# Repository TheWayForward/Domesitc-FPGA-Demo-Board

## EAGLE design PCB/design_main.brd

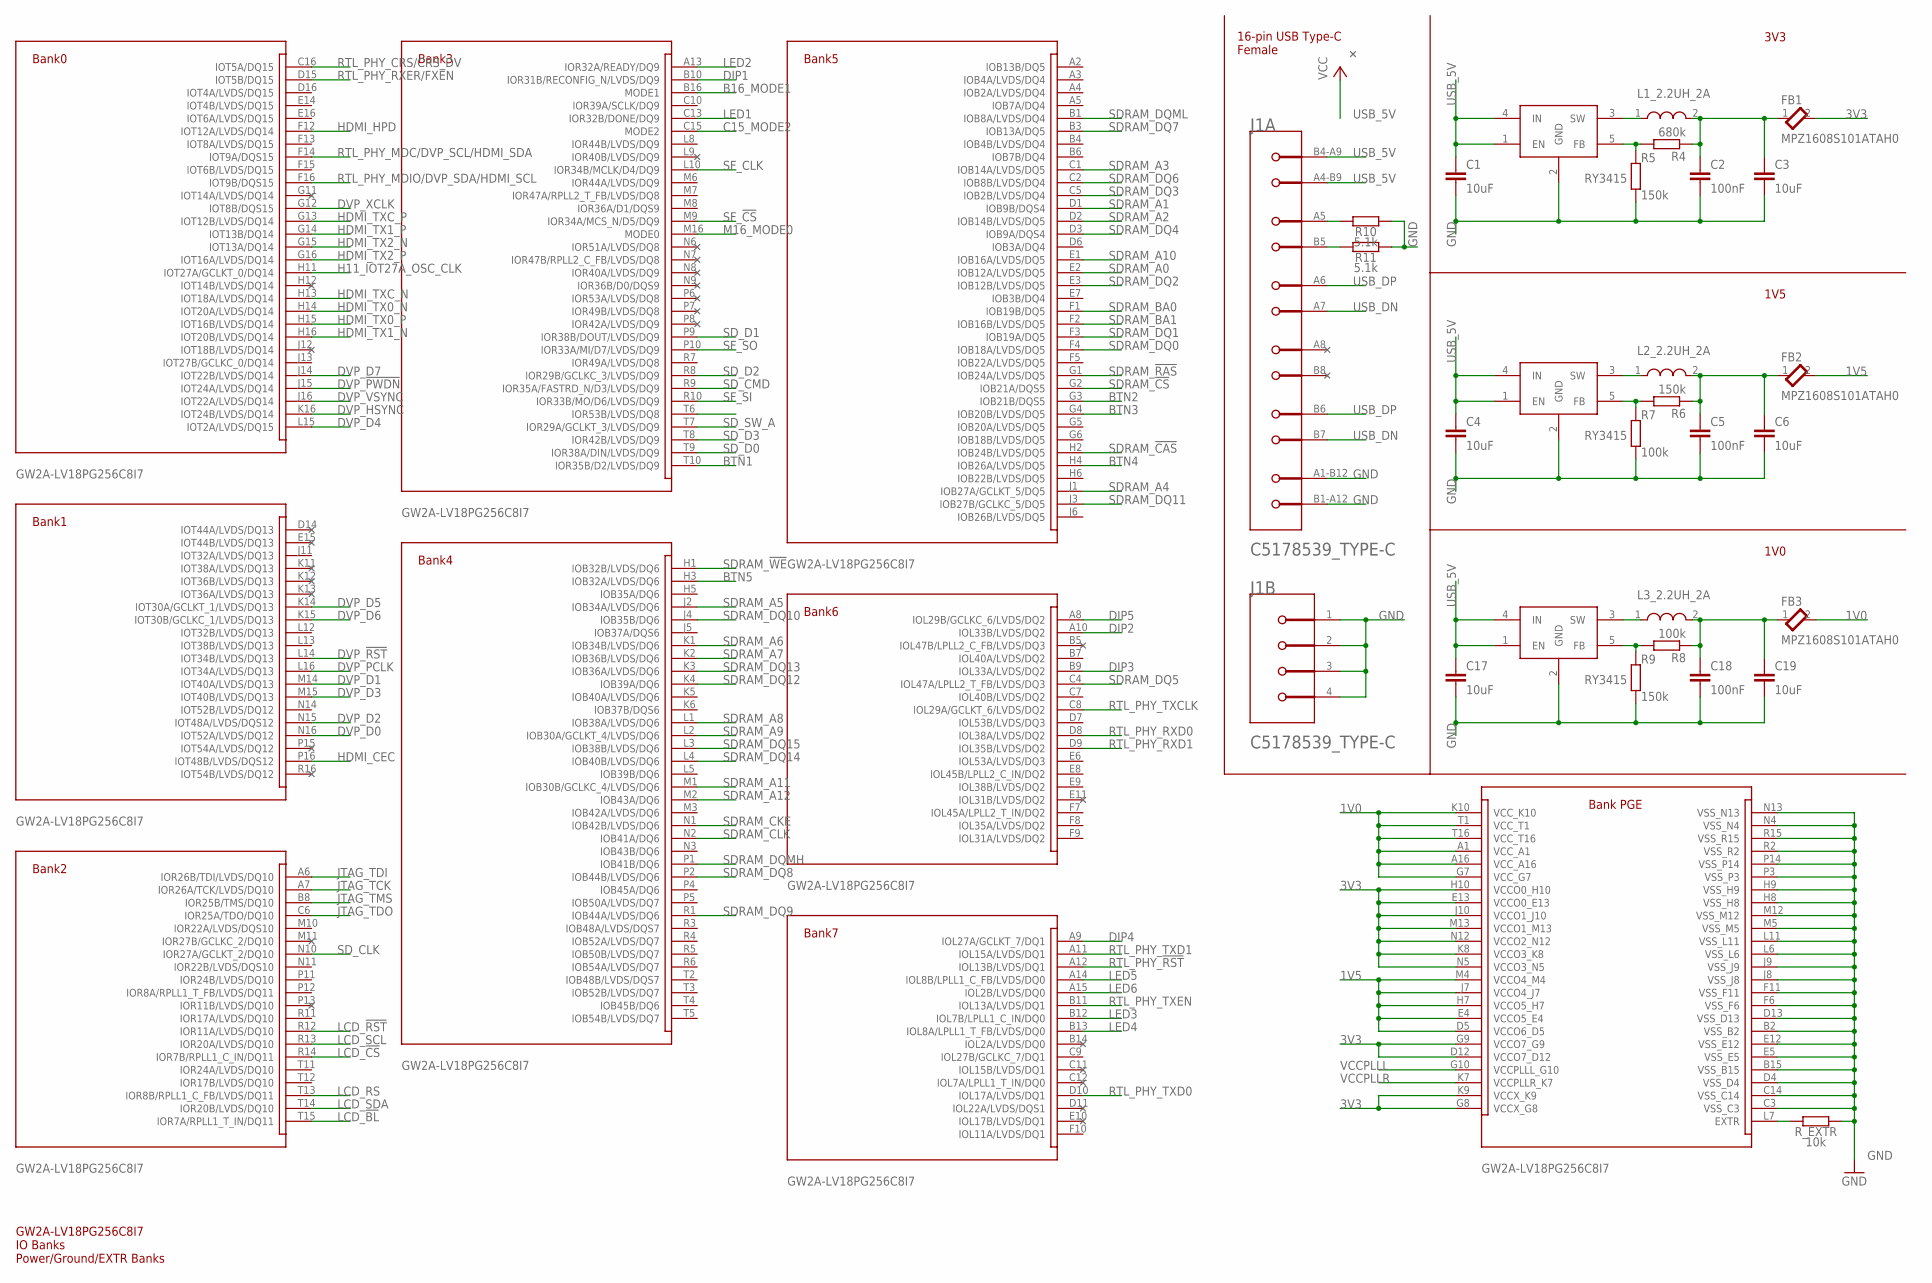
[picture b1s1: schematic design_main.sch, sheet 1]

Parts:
C1, C3, C4, C6, C17, C19: 10uF; C0805
C2, C5, C18: 100nF; C0805
FB1, FB2, FB3: TDK_MPZ1608S101ATAH0TDK_MPZ1608S101ATAH0_0_0; TDK_MPZ1608S101ATAH0_0
J1: C5178539_TYPE-CMOLEX_217179-0001_0_0; C5178539_TYPE-C
L1_2.2UH_2A: L_0805TDK_MLZ2012N6R8LT000_0_0; TDK_MLZ2012N6R8LT000_0
L2_2.2UH_2A, L3_2.2UH_2A: 2.2uH 2A; TDK_MLZ2012N6R8LT000_0
R4: 680k; R0805
R5, R6, R9: 150k; R0805
R7, R8: 100k; R0805
R10, R11: 5.1k; R0805
R_EXTR: 10k; R0805
U$1: GW2A-LV18PG256C8I7; BGA256C100P16X16_1700X1700X155
U$3, U$4, U$5: RY3415

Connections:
1V0: FB3.2, U$1.A1 (VCC_A1), U$1.A16 (VCC_A16), U$1.G7 (VCC_G7), U$1.K10 (VCC_K10), U$1.T1 (VCC_T1), U$1.T16 (VCC_T16); also elsewhere on the board
1V5: FB2.2, U$1.D5 (VCCO6_D5), U$1.E4 (VCCO5_E4), U$1.H7 (VCCO5_H7), U$1.J7 (VCCO4_J7), U$1.M4 (VCCO4_M4); also elsewhere on the board
3V3: FB1.2, U$1.D12 (VCCO7_D12), U$1.E13 (VCCO0_E13), U$1.G8 (VCCX_G8), U$1.G9 (VCCO7_G9), U$1.H10 (VCCO0_H10), U$1.J10 (VCCO1_J10), U$1.K8 (VCCO3_K8), U$1.K9 (VCCX_K9), U$1.M13 (VCCO1_M13), U$1.N5 (VCCO3_N5), U$1.N12 (VCCO2_N12); also elsewhere on the board
B16_MODE1: U$1.B16 (MODE1); also elsewhere on the board
BTN1: U$1.T10 (IOR35B/D2/LVDS/DQ9); also elsewhere on the board
BTN2: U$1.G3 (IOB21B/DQS5); also elsewhere on the board
BTN3: U$1.G4 (IOB20B/LVDS/DQ5); also elsewhere on the board
BTN4: U$1.H4 (IOB26A/LVDS/DQ5); also elsewhere on the board
BTN5: U$1.H3 (IOB32A/LVDS/DQ6); also elsewhere on the board
C15_MODE2: U$1.C15 (MODE2); also elsewhere on the board
DIP1: U$1.B10 (IOR31B/RECONFIG_N/LVDS/DQ9); also elsewhere on the board
DIP2: U$1.A10 (IOL33B/LVDS/DQ2); also elsewhere on the board
DIP3: U$1.B9 (IOL33A/LVDS/DQ2); also elsewhere on the board
DIP4: U$1.A9 (IOL27A/GCLKT_7/DQ1); also elsewhere on the board
DIP5: U$1.A8 (IOL29B/GCLKC_6/LVDS/DQ2); also elsewhere on the board
DVP_!PWDN!: U$1.J15 (IOT24A/LVDS/DQ14); also elsewhere on the board
DVP_!RST!: U$1.L14 (IOT34B/LVDS/DQ13); also elsewhere on the board
DVP_D0: U$1.N16 (IOT52A/LVDS/DQ12); also elsewhere on the board
DVP_D1: U$1.M14 (IOT40A/LVDS/DQ13); also elsewhere on the board
DVP_D2: U$1.N15 (IOT48A/LVDS/DQS12); also elsewhere on the board
DVP_D3: U$1.M15 (IOT40B/LVDS/DQ13); also elsewhere on the board
DVP_D4: U$1.L15 (IOT2A/LVDS/DQ15); also elsewhere on the board
DVP_D5: U$1.K14 (IOT30A/GCLKT_1/LVDS/DQ13); also elsewhere on the board
DVP_D6: U$1.K15 (IOT30B/GCLKC_1/LVDS/DQ13); also elsewhere on the board
DVP_D7: U$1.J14 (IOT22B/LVDS/DQ14); also elsewhere on the board
DVP_HSYNC: U$1.K16 (IOT24B/LVDS/DQ14); also elsewhere on the board
DVP_PCLK: U$1.L16 (IOT34A/LVDS/DQ13); also elsewhere on the board
DVP_VSYNC: U$1.J16 (IOT22A/LVDS/DQ14); also elsewhere on the board
DVP_XCLK: U$1.G12 (IOT8B/DQS15); also elsewhere on the board
GND: C1.1, C2.1, C3.1, C4.1, C5.1, C6.1, C17.1, C18.1, C19.1, J1.1 (MNT_1), J1.2 (MNT_2), J1.3 (MNT_3), J1.4 (MNT_4), J1.A1-B12 (1_GND), J1.B1-A12 (2_GND), R5.2, R7.2, R9.2, R10.1, R11.1, R_EXTR.2, U$1.B2 (VSS_B2), U$1.B15 (VSS_B15), U$1.C3 (VSS_C3), U$1.C14 (VSS_C14), U$1.D4 (VSS_D4), U$1.D13 (VSS_D13), U$1.E5 (VSS_E5), U$1.E12 (VSS_E12), U$1.F6 (VSS_F6), U$1.F11 (VSS_F11), U$1.H8 (VSS_H8), U$1.H9 (VSS_H9), U$1.J8 (VSS_J8), U$1.J9 (VSS_J9), U$1.L6 (VSS_L6), U$1.L11 (VSS_L11), U$1.M5 (VSS_M5), U$1.M12 (VSS_M12), U$1.N4 (VSS_N4), U$1.N13 (VSS_N13), U$1.P3 (VSS_P3), U$1.P14 (VSS_P14), U$1.R2 (VSS_R2), U$1.R15 (VSS_R15), U$3.2 (GND), U$4.2 (GND), U$5.2 (GND); also elsewhere on the board
H11_IOT27A_OSC_CLK: U$1.H11 (IOT27A/GCLKT_0/DQ14); also elsewhere on the board
HDMI_CEC: U$1.P16 (IOT48B/LVDS/DQS12); also elsewhere on the board
HDMI_HPD: U$1.F12 (IOT12A/LVDS/DQ14); also elsewhere on the board
HDMI_TX0_N: U$1.H14 (IOT20A/LVDS/DQ14); also elsewhere on the board
HDMI_TX0_P: U$1.H15 (IOT16B/LVDS/DQ14); also elsewhere on the board
HDMI_TX1_N: U$1.H16 (IOT20B/LVDS/DQ14); also elsewhere on the board
HDMI_TX1_P: U$1.G14 (IOT13B/DQ14); also elsewhere on the board
HDMI_TX2_N: U$1.G15 (IOT13A/DQ14); also elsewhere on the board
HDMI_TX2_P: U$1.G16 (IOT16A/LVDS/DQ14); also elsewhere on the board
HDMI_TXC_N: U$1.H13 (IOT18A/LVDS/DQ14); also elsewhere on the board
HDMI_TXC_P: U$1.G13 (IOT12B/LVDS/DQ14); also elsewhere on the board
JTAG_TCK: U$1.A7 (IOR26A/TCK/LVDS/DQ10); also elsewhere on the board
JTAG_TDI: U$1.A6 (IOR26B/TDI/LVDS/DQ10); also elsewhere on the board
JTAG_TDO: U$1.C6 (IOR25A/TDO/DQ10); also elsewhere on the board
JTAG_TMS: U$1.B8 (IOR25B/TMS/DQ10); also elsewhere on the board
LCD_!BL!: U$1.T15 (IOR7A/RPLL1_T_IN/DQ11); also elsewhere on the board
LCD_!CS!: U$1.R14 (IOR7B/RPLL1_C_IN/DQ11); also elsewhere on the board
LCD_!RST!: U$1.R12 (IOR11A/LVDS/DQ10); also elsewhere on the board
LCD_RS: U$1.T13 (IOR8B/RPLL1_C_FB/LVDS/DQ11); also elsewhere on the board
LCD_SCL: U$1.R13 (IOR20A/LVDS/DQ10); also elsewhere on the board
LCD_SDA: U$1.T14 (IOR20B/LVDS/DQ10); also elsewhere on the board
LED1: U$1.C13 (IOR32B/DONE/DQ9); also elsewhere on the board
LED2: U$1.A13 (IOR32A/READY/DQ9); also elsewhere on the board
LED3: U$1.B12 (IOL7B/LPLL1_C_IN/DQ0); also elsewhere on the board
LED4: U$1.B13 (IOL8A/LPLL1_T_FB/LVDS/DQ0); also elsewhere on the board
LED5: U$1.A14 (IOL8B/LPLL1_C_FB/LVDS/DQ0); also elsewhere on the board
LED6: U$1.A15 (IOL2B/LVDS/DQ0); also elsewhere on the board
M16_MODE0: U$1.M16 (MODE0); also elsewhere on the board
unnamed: R6.2, R7.1, U$4.5 (FB)
unnamed: R_EXTR.1, U$1.L7 (EXTR)
unnamed: L2_2.2UH_2A.1, U$4.3 (SW)
unnamed: C5.2, C6.2, FB2.1, L2_2.2UH_2A.2, R6.1
unnamed: R4.2, R5.1, U$3.5 (FB)
unnamed: L1_2.2UH_2A.1, U$3.3 (SW)
unnamed: C2.2, C3.2, FB1.1, L1_2.2UH_2A.2, R4.1
unnamed: R8.2, R9.1, U$5.5 (FB)
unnamed: L3_2.2UH_2A.1, U$5.3 (SW)
unnamed: C18.2, C19.2, FB3.1, L3_2.2UH_2A.2, R8.1
unnamed: J1.A5 (CC1), R10.2
unnamed: J1.B5 (CC2), R11.2
RTL_PHY_!RST!: U$1.A12 (IOL13B/LVDS/DQ1); also elsewhere on the board
RTL_PHY_CRS/CRS_DV: U$1.C16 (IOT5A/DQ15); also elsewhere on the board
RTL_PHY_MDC/DVP_SCL/HDMI_SDA: U$1.F14 (IOT9A/DQS15); also elsewhere on the board
RTL_PHY_MDIO/DVP_SDA/HDMI_SCL: U$1.F16 (IOT9B/DQS15); also elsewhere on the board
RTL_PHY_RXD0: U$1.D8 (IOL38A/LVDS/DQ2); also elsewhere on the board
RTL_PHY_RXD1: U$1.D9 (IOL35B/LVDS/DQ2); also elsewhere on the board
RTL_PHY_RXER/FXEN: U$1.D15 (IOT5B/DQ15); also elsewhere on the board
RTL_PHY_TXCLK: U$1.C8 (IOL29A/GCLKT_6/LVDS/DQ2); also elsewhere on the board
RTL_PHY_TXD0: U$1.D10 (IOL17A/LVDS/DQ1); also elsewhere on the board
RTL_PHY_TXD1: U$1.A11 (IOL15A/LVDS/DQ1); also elsewhere on the board
RTL_PHY_TXEN: U$1.B11 (IOL13A/LVDS/DQ1); also elsewhere on the board
SDRAM_!CAS!: U$1.H2 (IOB24B/LVDS/DQ5); also elsewhere on the board
SDRAM_!CS!: U$1.G2 (IOB21A/DQS5); also elsewhere on the board
SDRAM_!RAS!: U$1.G1 (IOB24A/LVDS/DQ5); also elsewhere on the board
SDRAM_!WE!: U$1.H1 (IOB32B/LVDS/DQ6); also elsewhere on the board
SDRAM_A0: U$1.E2 (IOB12A/LVDS/DQ5); also elsewhere on the board
SDRAM_A1: U$1.D1 (IOB9B/DQS4); also elsewhere on the board
SDRAM_A2: U$1.D2 (IOB14B/LVDS/DQ5); also elsewhere on the board
SDRAM_A3: U$1.C1 (IOB14A/LVDS/DQ5); also elsewhere on the board
SDRAM_A4: U$1.J1 (IOB27A/GCLKT_5/DQ5); also elsewhere on the board
SDRAM_A5: U$1.J2 (IOB34A/LVDS/DQ6); also elsewhere on the board
SDRAM_A6: U$1.K1 (IOB34B/LVDS/DQ6); also elsewhere on the board
SDRAM_A7: U$1.K2 (IOB36B/LVDS/DQ6); also elsewhere on the board
SDRAM_A8: U$1.L1 (IOB38A/LVDS/DQ6); also elsewhere on the board
SDRAM_A9: U$1.L2 (IOB30A/GCLKT_4/LVDS/DQ6); also elsewhere on the board
SDRAM_A10: U$1.E1 (IOB16A/LVDS/DQ5); also elsewhere on the board
SDRAM_A11: U$1.M1 (IOB30B/GCLKC_4/LVDS/DQ6); also elsewhere on the board
SDRAM_A12: U$1.M2 (IOB43A/DQ6); also elsewhere on the board
SDRAM_BA0: U$1.F1 (IOB19B/DQ5); also elsewhere on the board
SDRAM_BA1: U$1.F2 (IOB16B/LVDS/DQ5); also elsewhere on the board
SDRAM_CKE: U$1.N1 (IOB42B/LVDS/DQ6); also elsewhere on the board
SDRAM_CLK: U$1.N2 (IOB41A/DQ6); also elsewhere on the board
SDRAM_DQ0: U$1.F4 (IOB18A/LVDS/DQ5); also elsewhere on the board
SDRAM_DQ1: U$1.F3 (IOB19A/DQ5); also elsewhere on the board
SDRAM_DQ2: U$1.E3 (IOB12B/LVDS/DQ5); also elsewhere on the board
SDRAM_DQ3: U$1.C5 (IOB2B/LVDS/DQ4); also elsewhere on the board
SDRAM_DQ4: U$1.D3 (IOB9A/DQS4); also elsewhere on the board
SDRAM_DQ5: U$1.C4 (IOL47A/LPLL2_T_FB/LVDS/DQ3); also elsewhere on the board
SDRAM_DQ6: U$1.C2 (IOB8B/LVDS/DQ4); also elsewhere on the board
SDRAM_DQ7: U$1.B3 (IOB13A/DQ5); also elsewhere on the board
SDRAM_DQ8: U$1.P2 (IOB44B/LVDS/DQ6); also elsewhere on the board
SDRAM_DQ9: U$1.R1 (IOB44A/LVDS/DQ6); also elsewhere on the board
SDRAM_DQ10: U$1.J4 (IOB35B/DQ6); also elsewhere on the board
SDRAM_DQ11: U$1.J3 (IOB27B/GCLKC_5/DQ5); also elsewhere on the board
SDRAM_DQ12: U$1.K4 (IOB39A/DQ6); also elsewhere on the board
SDRAM_DQ13: U$1.K3 (IOB36A/LVDS/DQ6); also elsewhere on the board
SDRAM_DQ14: U$1.L4 (IOB40B/LVDS/DQ6); also elsewhere on the board
SDRAM_DQ15: U$1.L3 (IOB38B/LVDS/DQ6); also elsewhere on the board
SDRAM_DQMH: U$1.P1 (IOB41B/DQ6); also elsewhere on the board
SDRAM_DQML: U$1.B1 (IOB8A/LVDS/DQ4); also elsewhere on the board
SD_CLK: U$1.N10 (IOR27A/GCLKT_2/DQ10); also elsewhere on the board
SD_CMD: U$1.R9 (IOR35A/FASTRD_N/D3/LVDS/DQ9); also elsewhere on the board
SD_D0: U$1.T9 (IOR38A/DIN/LVDS/DQ9); also elsewhere on the board
SD_D1: U$1.P9 (IOR38B/DOUT/LVDS/DQ9); also elsewhere on the board
SD_D2: U$1.R8 (IOR29B/GCLKC_3/LVDS/DQ9); also elsewhere on the board
SD_D3: U$1.T8 (IOR42B/LVDS/DQ9); also elsewhere on the board
SD_SW_A: U$1.T7 (IOR29A/GCLKT_3/LVDS/DQ9); also elsewhere on the board
SF_!CS!: U$1.M9 (IOR34A/MCS_N/D5/DQ9); also elsewhere on the board
SF_CLK: U$1.L10 (IOR34B/MCLK/D4/DQ9); also elsewhere on the board
SF_SI: U$1.R10 (IOR33B/MO/D6/LVDS/DQ9); also elsewhere on the board
SF_SO: U$1.P10 (IOR33A/MI/D7/LVDS/DQ9); also elsewhere on the board
USB_5V: C1.2, C4.2, C17.2, J1.A4-B9 (1_VBUS), J1.B4-A9 (2_VBUS), U$3.1 (EN), U$3.4 (IN), U$4.1 (EN), U$4.4 (IN), U$5.1 (EN), U$5.4 (IN); also elsewhere on the board
USB_DN: J1.A7 (DN1), J1.B7 (DN2); also elsewhere on the board
USB_DP: J1.A6 (DP1), J1.B6 (DP2); also elsewhere on the board
VCCPLLL: U$1.G10 (VCCPLLL_G10); also elsewhere on the board
VCCPLLR: U$1.K7 (VCCPLLR_K7); also elsewhere on the board

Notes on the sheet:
3V3
1V5
1V0
16-pin USB Type-C Female
GW2A-LV18PG256C8I7 IO Banks Power/Ground/EXTR Banks

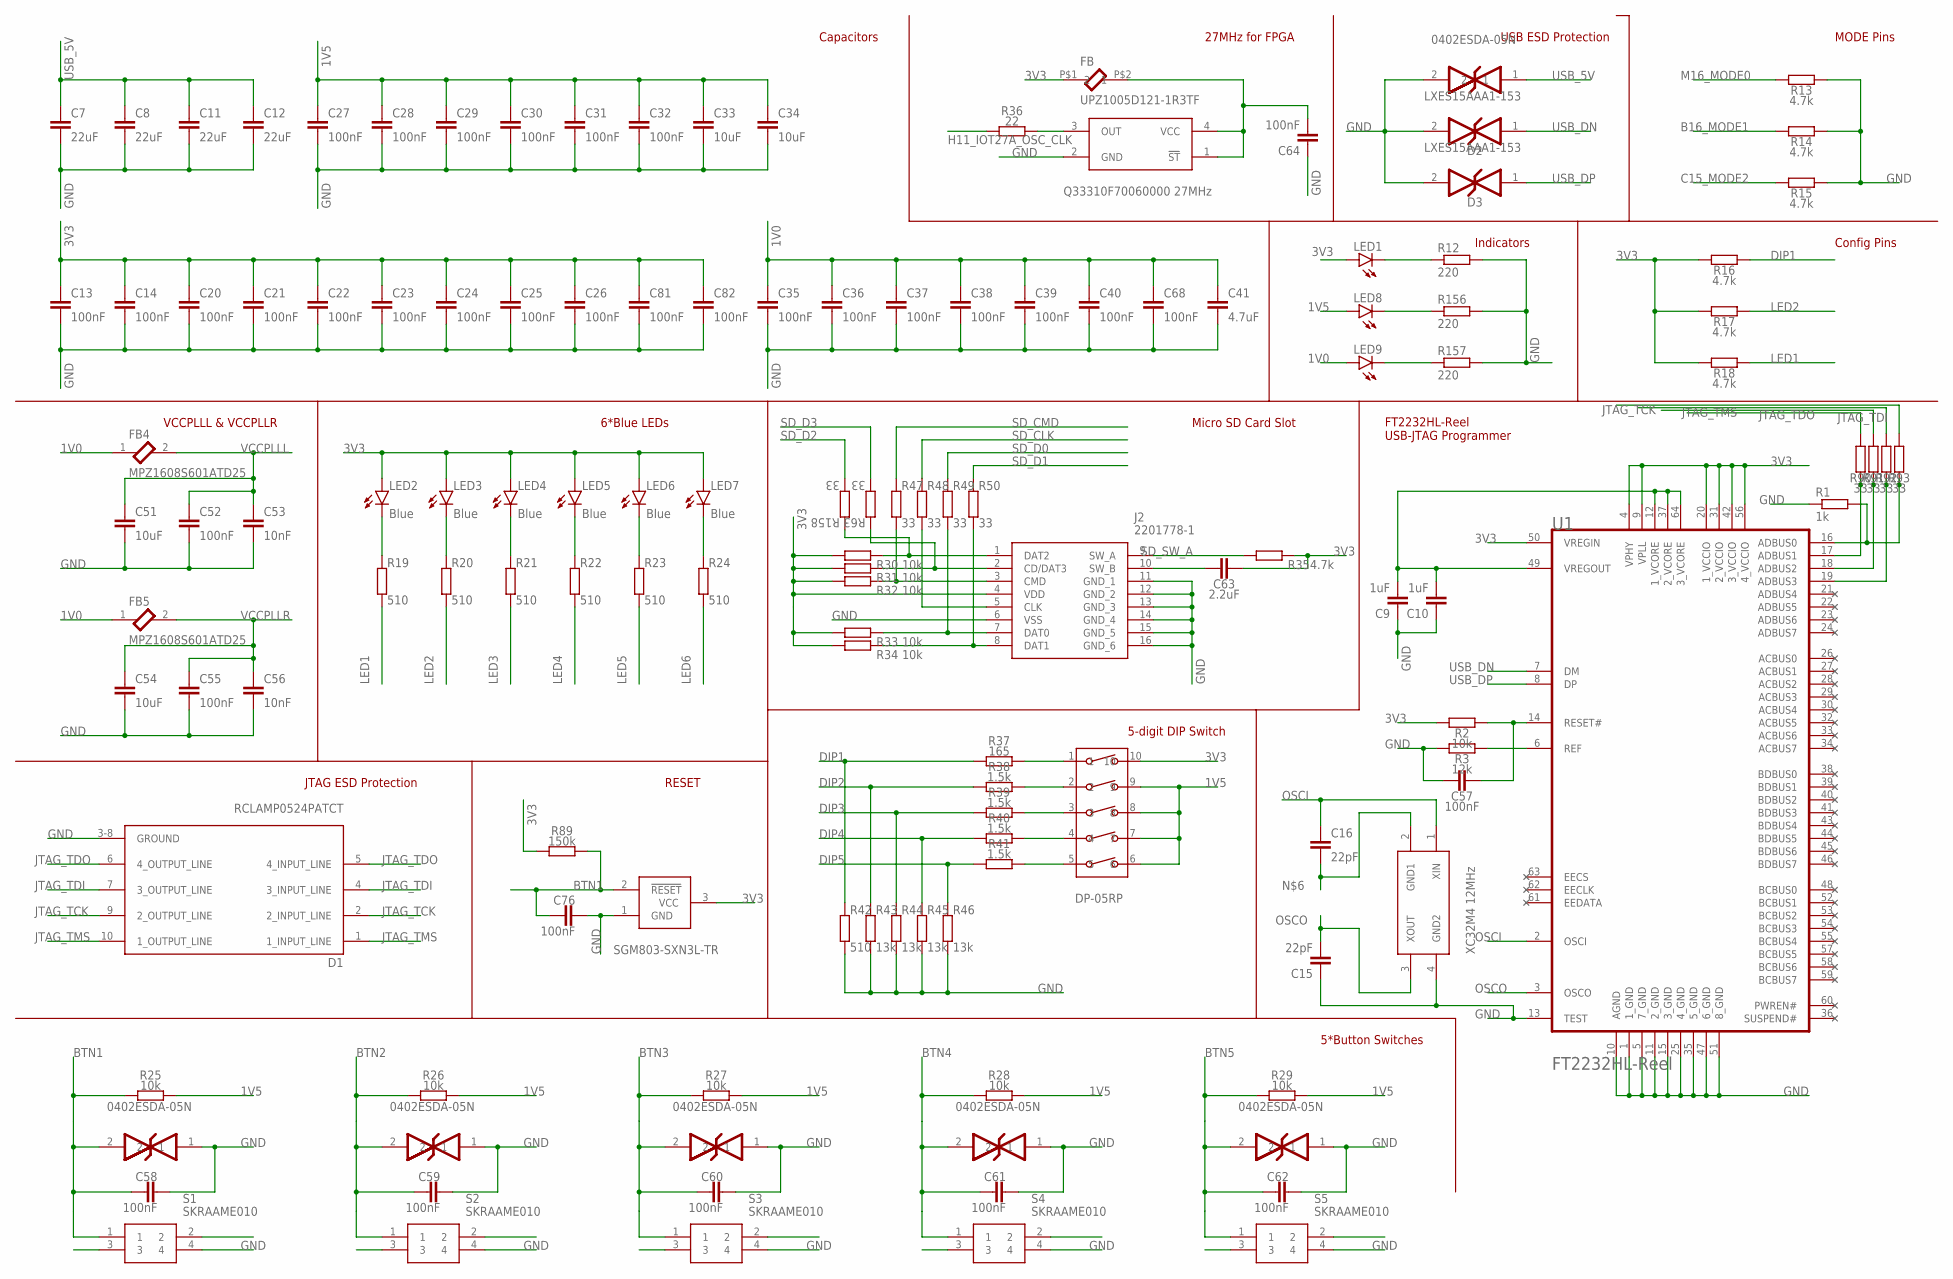
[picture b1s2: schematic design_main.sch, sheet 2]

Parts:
C7, C8, C11, C12: 22uF; C0805
C9, C10: 1uF; C0805
C13, C14, C20, C21, C22, C23, C24, C25, C26, C27, C28, C29, C30, C31, C32, C35, C36, C37, C38, C39, C40, C52, C55, C57, C58, C59, C60, C61, C62, C64, C68, C76, C81, C82: 100nF; C0805
C15, C16: 22pF; C0805
C33, C34, C51, C54: 10uF; C0805
C41: 4.7uF; C0805
C53, C56: 10nF; C0805
C63: 2.2uF; C0805
D1: SEMTECH_RCLAMP0524PATCTSEMTECH_RCLAMP0524PATCT_0_0; SEMTECH_RCLAMP0524PATCT_0
D2, D3: MURATA_LXES15AAA1-153MURATA_LXES15AAA1-153_0_0; MURATA_LXES15AAA1-153_0
FB: UPZ1005D121-1R3TF
FB4, FB5: TDK_MPZ1608S601ATD25TDK_MPZ1608S601ATD25_0_0; TDK_MPZ1608S601ATD25_0
J2: 2201778-1; 22017781
LED1, LED8, LED9: LEDSML0805; SML0805
LED2, LED3, LED4, LED5, LED6, LED7: Blue; SML0805
R1: 1k; R0805
R2, R25, R26, R27, R28, R29, R30, R31, R32, R33, R34: 10k; R0805
R3: 12k; R0805
R12, R156, R157: 220; R0805
R13, R14, R15, R16, R17, R18, R35: 4.7k; R0805
R19, R20, R21, R22, R23, R24, R42: 510; R0805
R36: 22; R0805
R37: 165; R0805
R38, R39, R40, R41: 1.5k; R0805
R43, R44, R45, R46: 13k; R0805
R47, R48, R49, R50, R63, R90, R91, R92, R93, R158: 33; R0805
R89: 150k; R0805
S1, S2, S3, S4, S5: SKRAAME010
U1: FTDI_FT2232HL-REELFTDI_FT2232HL-REEL_0_0; FTDI_FT2232HL-REEL_0
U$2: XC32M4-12MHZ
U$6, U$7, U$8, U$9, U$10, U$11: 0402ESDA-05N
U$13: DP-05RP
U$15: Q33310F70060000-27MHZ
U$16: SGM803-SXN3L-TR

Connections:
1V0: C35.2, C36.2, C37.2, C38.2, C39.2, C40.2, C41.2, C68.2, FB4.1, FB5.1, LED9.A; also elsewhere on the board
1V5: C27.2, C28.2, C29.2, C30.2, C31.2, C32.2, C33.2, C34.2, LED8.A, R25.2, R26.2, R27.2, R28.2, R29.2, U$13.6, U$13.7, U$13.8, U$13.9; also elsewhere on the board
3V3: C13.2, C14.2, C20.2, C21.2, C22.2, C23.2, C24.2, C25.2, C26.2, C63.1, C81.2, C82.2, FB.P$1 (1), J2.4 (VDD), LED1.A, LED2.A, LED3.A, LED4.A, LED5.A, LED6.A, LED7.A, R2.1, R16.2, R17.2, R18.2, R30.1, R31.1, R32.1, R33.1, R34.1, R35.2, R89.1, U1.4 (VPHY), U1.9 (VPLL), U1.20 (1_VCCIO), U1.31 (2_VCCIO), U1.42 (3_VCCIO), U1.50 (VREGIN), U1.56 (4_VCCIO), U$13.10, U$16.3 (VCC); also elsewhere on the board
B16_MODE1: R14.2; also elsewhere on the board
BTN1: C58.2, C76.2, R25.1, R89.2, S1.1, U$7.2, U$16.2 (!RESET!); also elsewhere on the board
BTN2: C59.2, R26.1, S2.1, U$8.2; also elsewhere on the board
BTN3: C60.2, R27.1, S3.1, U$9.2; also elsewhere on the board
BTN4: C61.2, R28.1, S4.1, U$10.2; also elsewhere on the board
BTN5: C62.2, R29.1, S5.1, U$11.2; also elsewhere on the board
C15_MODE2: R15.2; also elsewhere on the board
DIP1: R16.1, R37.1, R42.2; also elsewhere on the board
DIP2: R38.1, R43.2; also elsewhere on the board
DIP3: R39.1, R44.2; also elsewhere on the board
DIP4: R40.1, R45.2; also elsewhere on the board
DIP5: R41.1, R46.2; also elsewhere on the board
GND: C7.1, C8.1, C9.1, C10.1, C11.1, C12.1, C13.1, C14.1, C15.1, C20.1, C21.1, C22.1, C23.1, C24.1, C25.1, C26.1, C27.1, C28.1, C29.1, C30.1, C31.1, C32.1, C33.1, C34.1, C35.1, C36.1, C37.1, C38.1, C39.1, C40.1, C41.1, C51.1, C52.1, C53.1, C54.1, C55.1, C56.1, C57.2, C58.1, C59.1, C60.1, C61.1, C62.1, C64.1, C68.1, C76.1, C81.1, C82.1, D1.3-8 (GROUND), D2.2, D3.2, J2.6 (VSS), J2.11 (GND_1), J2.12 (GND_2), J2.13 (GND_3), J2.14 (GND_4), J2.15 (GND_5), J2.16 (GND_6), R1.1, R3.1, R12.2, R13.1, R14.1, R15.1, R42.1, R43.1, R44.1, R45.1, R46.1, R156.2, R157.2, S1.4, S2.4, S3.4, S4.4, S5.4, U1.1 (1_GND), U1.5 (7_GND), U1.10 (AGND), U1.11 (2_GND), U1.13 (TEST), U1.15 (3_GND), U1.25 (4_GND), U1.35 (5_GND), U1.47 (6_GND), U1.51 (8_GND), U$2.4 (GND2), U$6.2, U$7.1, U$8.1, U$9.1, U$10.1, U$11.1, U$15.2 (GND), U$16.1 (GND); also elsewhere on the board
H11_IOT27A_OSC_CLK: R36.2; also elsewhere on the board
JTAG_TCK: D1.2 (2_INPUT_LINE), D1.9 (2_OUTPUT_LINE), R93.1; also elsewhere on the board
JTAG_TDI: D1.4 (3_INPUT_LINE), D1.7 (3_OUTPUT_LINE), R90.1; also elsewhere on the board
JTAG_TDO: D1.5 (4_INPUT_LINE), D1.6 (4_OUTPUT_LINE), R91.1; also elsewhere on the board
JTAG_TMS: D1.1 (1_INPUT_LINE), D1.10 (1_OUTPUT_LINE), R92.1; also elsewhere on the board
LED1: R18.1, R19.2; also elsewhere on the board
LED2: R17.1, R20.2; also elsewhere on the board
LED3: R21.2; also elsewhere on the board
LED4: R22.2; also elsewhere on the board
LED5: R23.2; also elsewhere on the board
LED6: R24.2; also elsewhere on the board
M16_MODE0: R13.2; also elsewhere on the board
unnamed: R39.2, U$13.3
unnamed: C16.1, U$2.2 (GND1)
unnamed: R3.2, U1.6 (REF)
unnamed: C57.1, R2.2, U1.14 (RESET#)
unnamed: C63.2, J2.10 (SW_B)
unnamed: J2.2 (CD/DAT3), R31.2, R63.1
unnamed: C9.2, C10.2, U1.12 (1_VCORE), U1.37 (2_VCORE), U1.49 (VREGOUT), U1.64 (3_VCORE)
unnamed: LED1.C, R12.1
unnamed: J2.3 (CMD), R32.2, R47.2
unnamed: LED2.C, R19.1
unnamed: LED3.C, R20.1
unnamed: LED4.C, R21.1
unnamed: LED5.C, R22.1
unnamed: LED6.C, R23.1
unnamed: LED7.C, R24.1
unnamed: C64.2, FB.P$2 (2), U$15.1 (!ST!), U$15.4 (VCC)
unnamed: R36.1, U$15.3 (OUT)
unnamed: R37.2, U$13.1
unnamed: R38.2, U$13.2
unnamed: R40.2, U$13.4
unnamed: R41.2, U$13.5
unnamed: J2.5 (CLK), R48.2
unnamed: J2.7 (DAT0), R33.2, R49.2
unnamed: J2.8 (DAT1), R34.2, R50.2
unnamed: J2.1 (DAT2), R30.2, R158.1
unnamed: R1.2, R93.2, U1.16 (ADBUS0)
unnamed: R90.2, U1.17 (ADBUS1)
unnamed: R91.2, U1.18 (ADBUS2)
unnamed: R92.2, U1.19 (ADBUS3)
unnamed: LED8.C, R156.1
unnamed: LED9.C, R157.1
OSCI: C16.2, U1.2 (OSCI), U$2.1 (XIN)
OSCO: C15.2, U1.3 (OSCO), U$2.3 (XOUT)
SD_CLK: R48.1; also elsewhere on the board
SD_CMD: R47.1; also elsewhere on the board
SD_D0: R49.1; also elsewhere on the board
SD_D1: R50.1; also elsewhere on the board
SD_D2: R158.2; also elsewhere on the board
SD_D3: R63.2; also elsewhere on the board
SD_SW_A: J2.9 (SW_A), R35.1; also elsewhere on the board
USB_5V: C7.2, C8.2, C11.2, C12.2, U$6.1; also elsewhere on the board
USB_DN: D2.1, U1.7 (DM); also elsewhere on the board
USB_DP: D3.1, U1.8 (DP); also elsewhere on the board
VCCPLLL: C51.2, C52.2, C53.2, FB4.2; also elsewhere on the board
VCCPLLR: C54.2, C55.2, C56.2, FB5.2; also elsewhere on the board

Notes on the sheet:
Capacitors
27MHz for FPGA
USB ESD Protection
MODE Pins
Indicators
Config Pins
FT2232HL-Reel USB-JTAG Programmer
Micro SD Card Slot
6*Blue LEDs
VCCPLLL & VCCPLLR
RESET
JTAG ESD Protection
5-digit DIP Switch
5*Button Switches

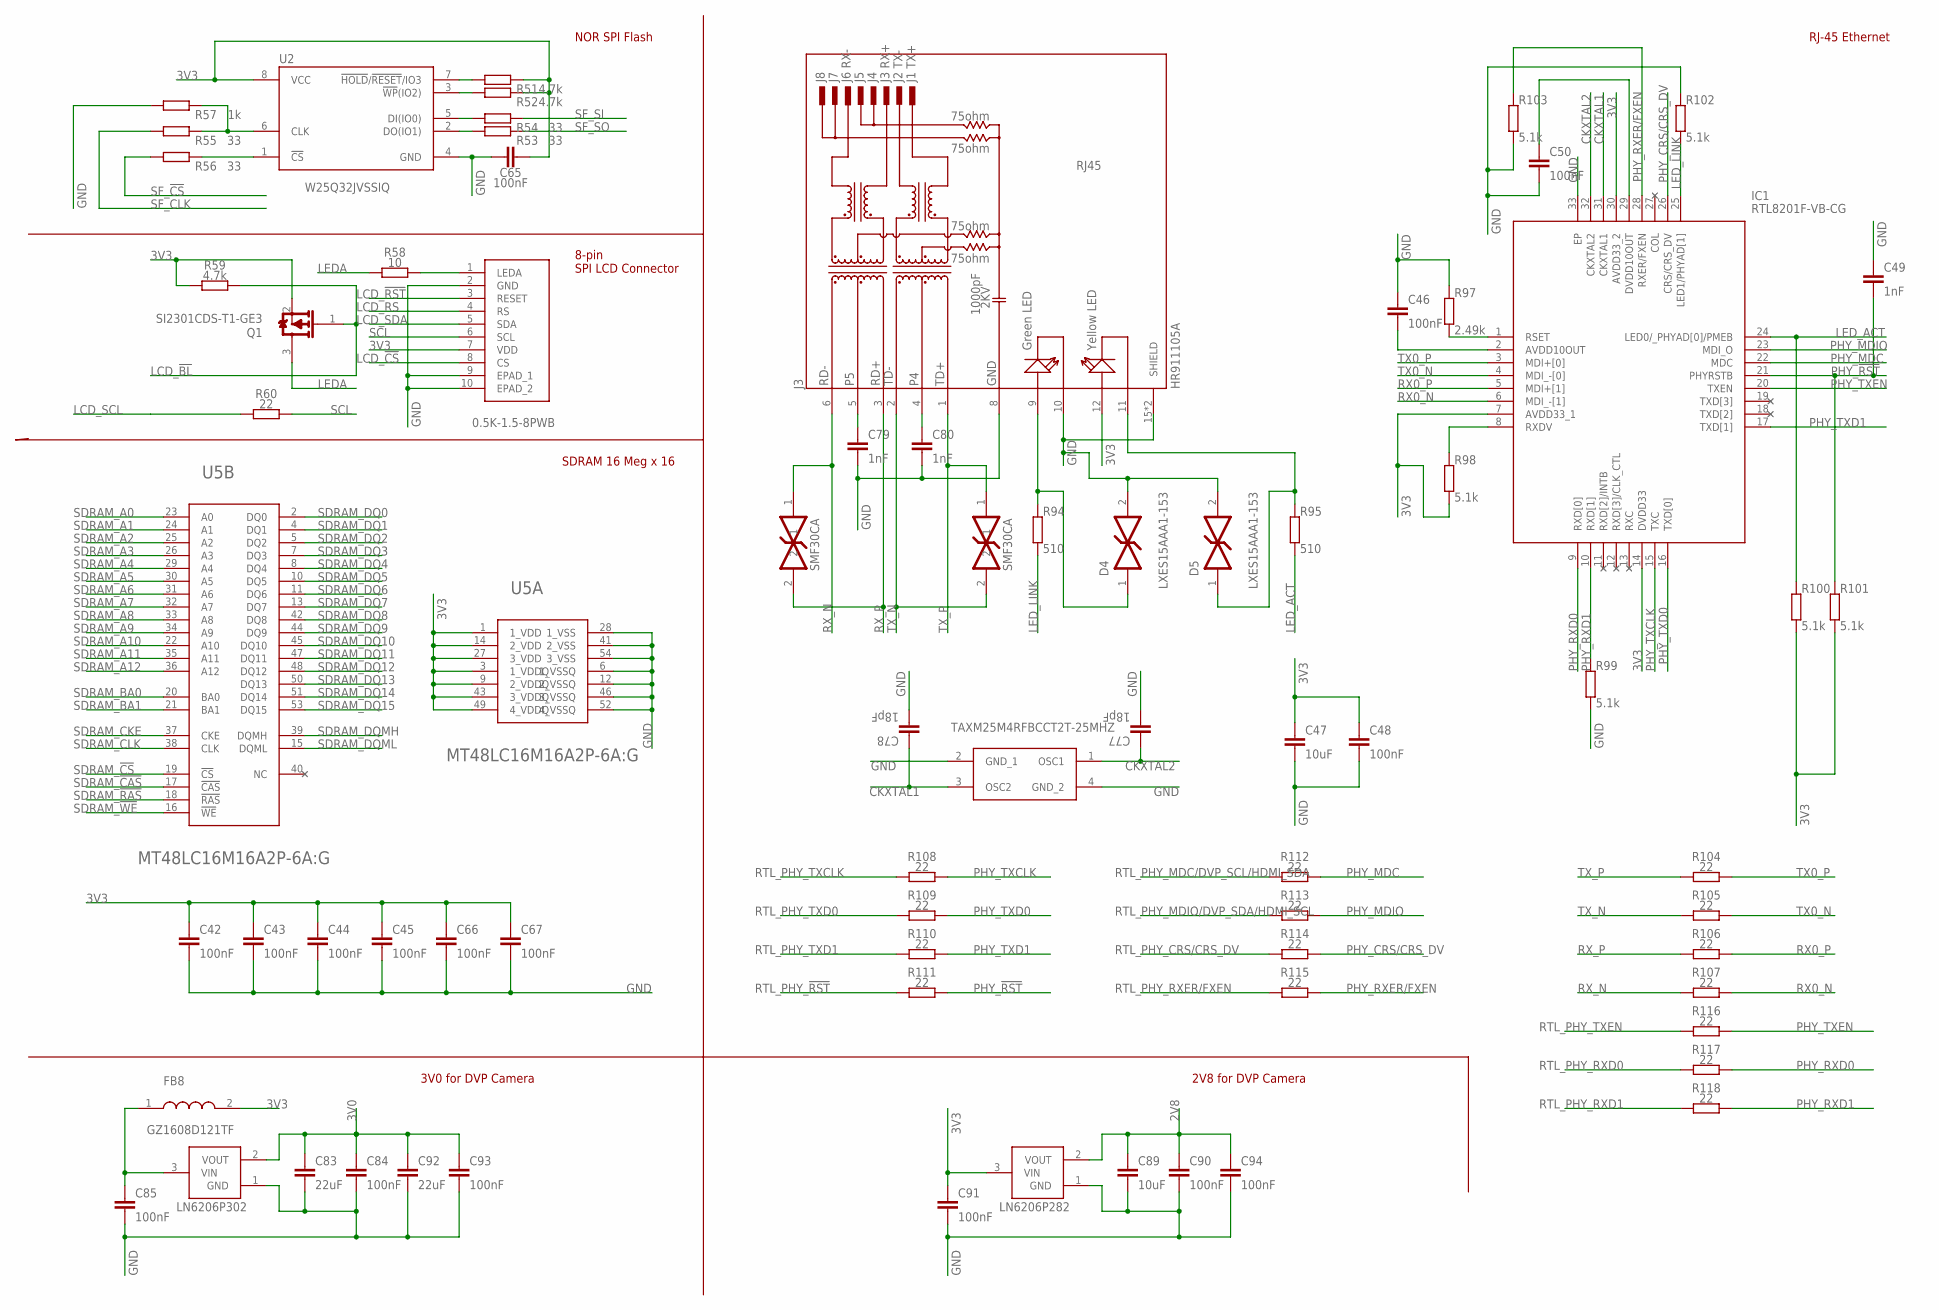
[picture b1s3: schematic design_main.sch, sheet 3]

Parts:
C42, C43, C44, C45, C46, C48, C50, C65, C66, C67, C84, C85, C90, C91, C93, C94: 100nF; C0805
C47, C89: 10uF; C0805
C49, C79, C80: 1nF; C0805
C77, C78: 18pF; C0805
C83, C92: 22uF; C0805
D4, D5: MURATA_LXES15AAA1-153MURATA_LXES15AAA1-153_0_0; MURATA_LXES15AAA1-153_0
FB8: SUNLORD_GZ1608D121TFSUNLORD_GZ1608D121TF_0_0; SUNLORD_GZ1608D121TF_0
IC1: RTL8201F-VB-CG; QFN50P500X500X100-33N
J3: HR911105A; HANRUN_HR911105A
Q1: VISHAY_SI2301CDS-T1-GE3VISHAY_SI2301CDS-T1-GE3_0_0; VISHAY_SI2301CDS-T1-GE3_0
R51, R52, R59: 4.7k; R0805
R53, R54, R55, R56: 33; R0805
R57: 1k; R0805
R58: 10; R0805
R60, R104, R105, R106, R107, R108, R109, R110, R111, R112, R113, R114, R115, R116, R117, R118: 22; R0805
R94, R95: 510; R0805
R97: 2.49k; R0805
R98, R99, R100, R101, R102, R103: 5.1k; R0805
U2: WINBOND_W25Q32JVSSIQWINBOND_W25Q32JVSSIQ_0_0; WINBOND_W25Q32JVSSIQ_0
U5: MICRON_MT48LC16M16A2P-6A-GMICRON_MT48LC16M16A2P-6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; MICRON_MT48LC16M16A2P-6A-G_0
U$14: 0.5K-1.5-8PWB
U$17: TAXM25M4RFBCCT2T-25MHZ
U$18, U$19: SMF30CA
U$20: LN6206P302
U$22: LN6206P282

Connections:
2V8: C89.2, C90.2, C94.2, U$22.2 (VOUT); also elsewhere on the board
3V0: C83.2, C84.2, C92.2, C93.2, U$20.2 (VOUT); also elsewhere on the board
3V3: C42.2, C43.2, C44.2, C45.2, C47.2, C48.2, C65.1, C66.2, C67.2, C91.2, FB8.2, IC1.7 (AVDD33_1), IC1.14 (DVDD33), IC1.30 (AVDD33_2), J3.12 (YA), Q1.2 (S), R51.2, R52.2, R59.1, R98.1, R100.1, R101.1, U2.8 (VCC), U5.1 (1_VDD), U5.3 (1_VDDQ), U5.9 (2_VDDQ), U5.14 (2_VDD), U5.27 (3_VDD), U5.43 (3_VDDQ), U5.49 (4_VDDQ), U$14.7 (VDD), U$22.3 (VIN); also elsewhere on the board
CKXTAL1: C78.2, IC1.31 (CKXTAL1), U$17.3 (OSC2)
CKXTAL2: C77.2, IC1.32 (CKXTAL2), U$17.1 (OSC1)
GND: C42.1, C43.1, C44.1, C45.1, C46.2, C47.1, C48.1, C49.2, C50.1, C65.2, C66.1, C67.1, C77.1, C78.1, C79.1, C80.1, C83.1, C84.1, C85.1, C89.1, C90.1, C91.1, C92.1, C93.1, C94.1, D4.2, D5.2, IC1.33 (EP), J3.8 (GND), J3.10 (GC), J3.15 (SHIELD), J3.16 (SHIELD), R57.1, R97.1, R99.1, R102.1, R103.2, U2.4 (GND), U5.6 (1_VSSQ), U5.12 (2_VSSQ), U5.28 (1_VSS), U5.41 (2_VSS), U5.46 (3_VSSQ), U5.52 (4_VSSQ), U5.54 (3_VSS), U$14.2 (GND), U$14.9 (EPAD_1), U$14.10 (EPAD_2), U$17.2 (GND_1), U$17.4 (GND_2), U$20.1 (GND), U$22.1 (GND); also elsewhere on the board
LCD_!BL!: Q1.1 (G), R59.2; also elsewhere on the board
LCD_!CS!: U$14.8 (CS); also elsewhere on the board
LCD_!RST!: U$14.3 (RESET); also elsewhere on the board
LCD_RS: U$14.4 (RS); also elsewhere on the board
LCD_SCL: R60.1; also elsewhere on the board
LCD_SDA: U$14.5 (SDA); also elsewhere on the board
LEDA: Q1.3 (D), R58.1
LED_ACT: IC1.24 (LED0/_PHYAD[0]/PMEB), R95.2, R100.2
LED_LINK: IC1.25 (LED1/PHYAD[1]), R94.2, R102.2
unnamed: R52.1, U2.3 (!WP!(IO2))
unnamed: R58.2, U$14.1 (LEDA)
unnamed: R51.1, U2.7 (!HOLD!/!RESET!/IO3)
unnamed: R53.1, U2.2 (DO(IO1))
unnamed: R54.1, U2.5 (DI(IO0))
unnamed: R55.2, R57.2, U2.6 (CLK)
unnamed: R56.2, U2.1 (!CS!)
unnamed: IC1.1 (RSET), R97.2
unnamed: C46.1, IC1.2 (AVDD10OUT)
unnamed: C79.2, J3.5
unnamed: C80.2, J3.4
unnamed: D4.1, J3.9 (GA), R94.1
unnamed: D5.1, J3.11 (YC), R95.1
unnamed: IC1.8 (RXDV), R98.2
unnamed: C50.2, IC1.29 (DVDD10OUT)
unnamed: C85.2, FB8.1, U$20.3 (VIN)
PHY_!RST!: C49.1, IC1.21 (PHYRSTB), R101.2, R111.2
PHY_CRS/CRS_DV: IC1.26 (CRS/CRS_DV), R114.2
PHY_MDC: IC1.22 (MDC), R112.2
PHY_MDIO: IC1.23 (MDI_O), R113.2
PHY_RXD0: IC1.9 (RXD[0]), R117.2
PHY_RXD1: IC1.10 (RXD[1]), R99.2, R118.2
PHY_RXER/FXEN: IC1.28 (RXER/FXEN), R103.1, R115.2
PHY_TXCLK: IC1.15 (TXC), R108.2
PHY_TXD0: IC1.16 (TXD[0]), R109.2
PHY_TXD1: IC1.17 (TXD[1]), R110.2
PHY_TXEN: IC1.20 (TXEN), R116.2
RTL_PHY_!RST!: R111.1; also elsewhere on the board
RTL_PHY_CRS/CRS_DV: R114.1; also elsewhere on the board
RTL_PHY_MDC/DVP_SCL/HDMI_SDA: R112.1; also elsewhere on the board
RTL_PHY_MDIO/DVP_SDA/HDMI_SCL: R113.1; also elsewhere on the board
RTL_PHY_RXD0: R117.1; also elsewhere on the board
RTL_PHY_RXD1: R118.1; also elsewhere on the board
RTL_PHY_RXER/FXEN: R115.1; also elsewhere on the board
RTL_PHY_TXCLK: R108.1; also elsewhere on the board
RTL_PHY_TXD0: R109.1; also elsewhere on the board
RTL_PHY_TXD1: R110.1; also elsewhere on the board
RTL_PHY_TXEN: R116.1; also elsewhere on the board
RX0_N: IC1.6 (MDI_-[1]), R107.2
RX0_P: IC1.5 (MDI+[1]), R106.2
RX_N: J3.6 (RD-), R107.1, U$18.1
RX_P: J3.3 (RD+), R106.1, U$18.2
SCL: R60.2, U$14.6 (SCL)
SDRAM_!CAS!: U5.17 (!CAS!); also elsewhere on the board
SDRAM_!CS!: U5.19 (!CS!); also elsewhere on the board
SDRAM_!RAS!: U5.18 (!RAS!); also elsewhere on the board
SDRAM_!WE!: U5.16 (!WE!); also elsewhere on the board
SDRAM_A0: U5.23 (A0); also elsewhere on the board
SDRAM_A1: U5.24 (A1); also elsewhere on the board
SDRAM_A2: U5.25 (A2); also elsewhere on the board
SDRAM_A3: U5.26 (A3); also elsewhere on the board
SDRAM_A4: U5.29 (A4); also elsewhere on the board
SDRAM_A5: U5.30 (A5); also elsewhere on the board
SDRAM_A6: U5.31 (A6); also elsewhere on the board
SDRAM_A7: U5.32 (A7); also elsewhere on the board
SDRAM_A8: U5.33 (A8); also elsewhere on the board
SDRAM_A9: U5.34 (A9); also elsewhere on the board
SDRAM_A10: U5.22 (A10); also elsewhere on the board
SDRAM_A11: U5.35 (A11); also elsewhere on the board
SDRAM_A12: U5.36 (A12); also elsewhere on the board
SDRAM_BA0: U5.20 (BA0); also elsewhere on the board
SDRAM_BA1: U5.21 (BA1); also elsewhere on the board
SDRAM_CKE: U5.37 (CKE); also elsewhere on the board
SDRAM_CLK: U5.38 (CLK); also elsewhere on the board
SDRAM_DQ0: U5.2 (DQ0); also elsewhere on the board
SDRAM_DQ1: U5.4 (DQ1); also elsewhere on the board
SDRAM_DQ2: U5.5 (DQ2); also elsewhere on the board
SDRAM_DQ3: U5.7 (DQ3); also elsewhere on the board
SDRAM_DQ4: U5.8 (DQ4); also elsewhere on the board
SDRAM_DQ5: U5.10 (DQ5); also elsewhere on the board
SDRAM_DQ6: U5.11 (DQ6); also elsewhere on the board
SDRAM_DQ7: U5.13 (DQ7); also elsewhere on the board
SDRAM_DQ8: U5.42 (DQ8); also elsewhere on the board
SDRAM_DQ9: U5.44 (DQ9); also elsewhere on the board
SDRAM_DQ10: U5.45 (DQ10); also elsewhere on the board
SDRAM_DQ11: U5.47 (DQ11); also elsewhere on the board
SDRAM_DQ12: U5.48 (DQ12); also elsewhere on the board
SDRAM_DQ13: U5.50 (DQ13); also elsewhere on the board
SDRAM_DQ14: U5.51 (DQ14); also elsewhere on the board
SDRAM_DQ15: U5.53 (DQ15); also elsewhere on the board
SDRAM_DQMH: U5.39 (DQMH); also elsewhere on the board
SDRAM_DQML: U5.15 (DQML); also elsewhere on the board
SF_!CS!: R56.1; also elsewhere on the board
SF_CLK: R55.1; also elsewhere on the board
SF_SI: R54.2; also elsewhere on the board
SF_SO: R53.2; also elsewhere on the board
TX0_N: IC1.4 (MDI_-[0]), R105.2
TX0_P: IC1.3 (MDI+[0]), R104.2
TX_N: J3.2 (TD-), R105.1, U$19.2
TX_P: J3.1 (TD+), R104.1, U$19.1

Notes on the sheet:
RJ45
NOR SPI Flash
8-pin SPI LCD Connector
SDRAM 16 Meg x 16
RJ-45 Ethernet
3V0 for DVP Camera
2V8 for DVP Camera

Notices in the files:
parts and their libraries:
SparkFun-Connectors: Licensing: Creative Commons ShareAlike 4.0 International - https://creativecommons.org/licenses/by-sa/4.0
